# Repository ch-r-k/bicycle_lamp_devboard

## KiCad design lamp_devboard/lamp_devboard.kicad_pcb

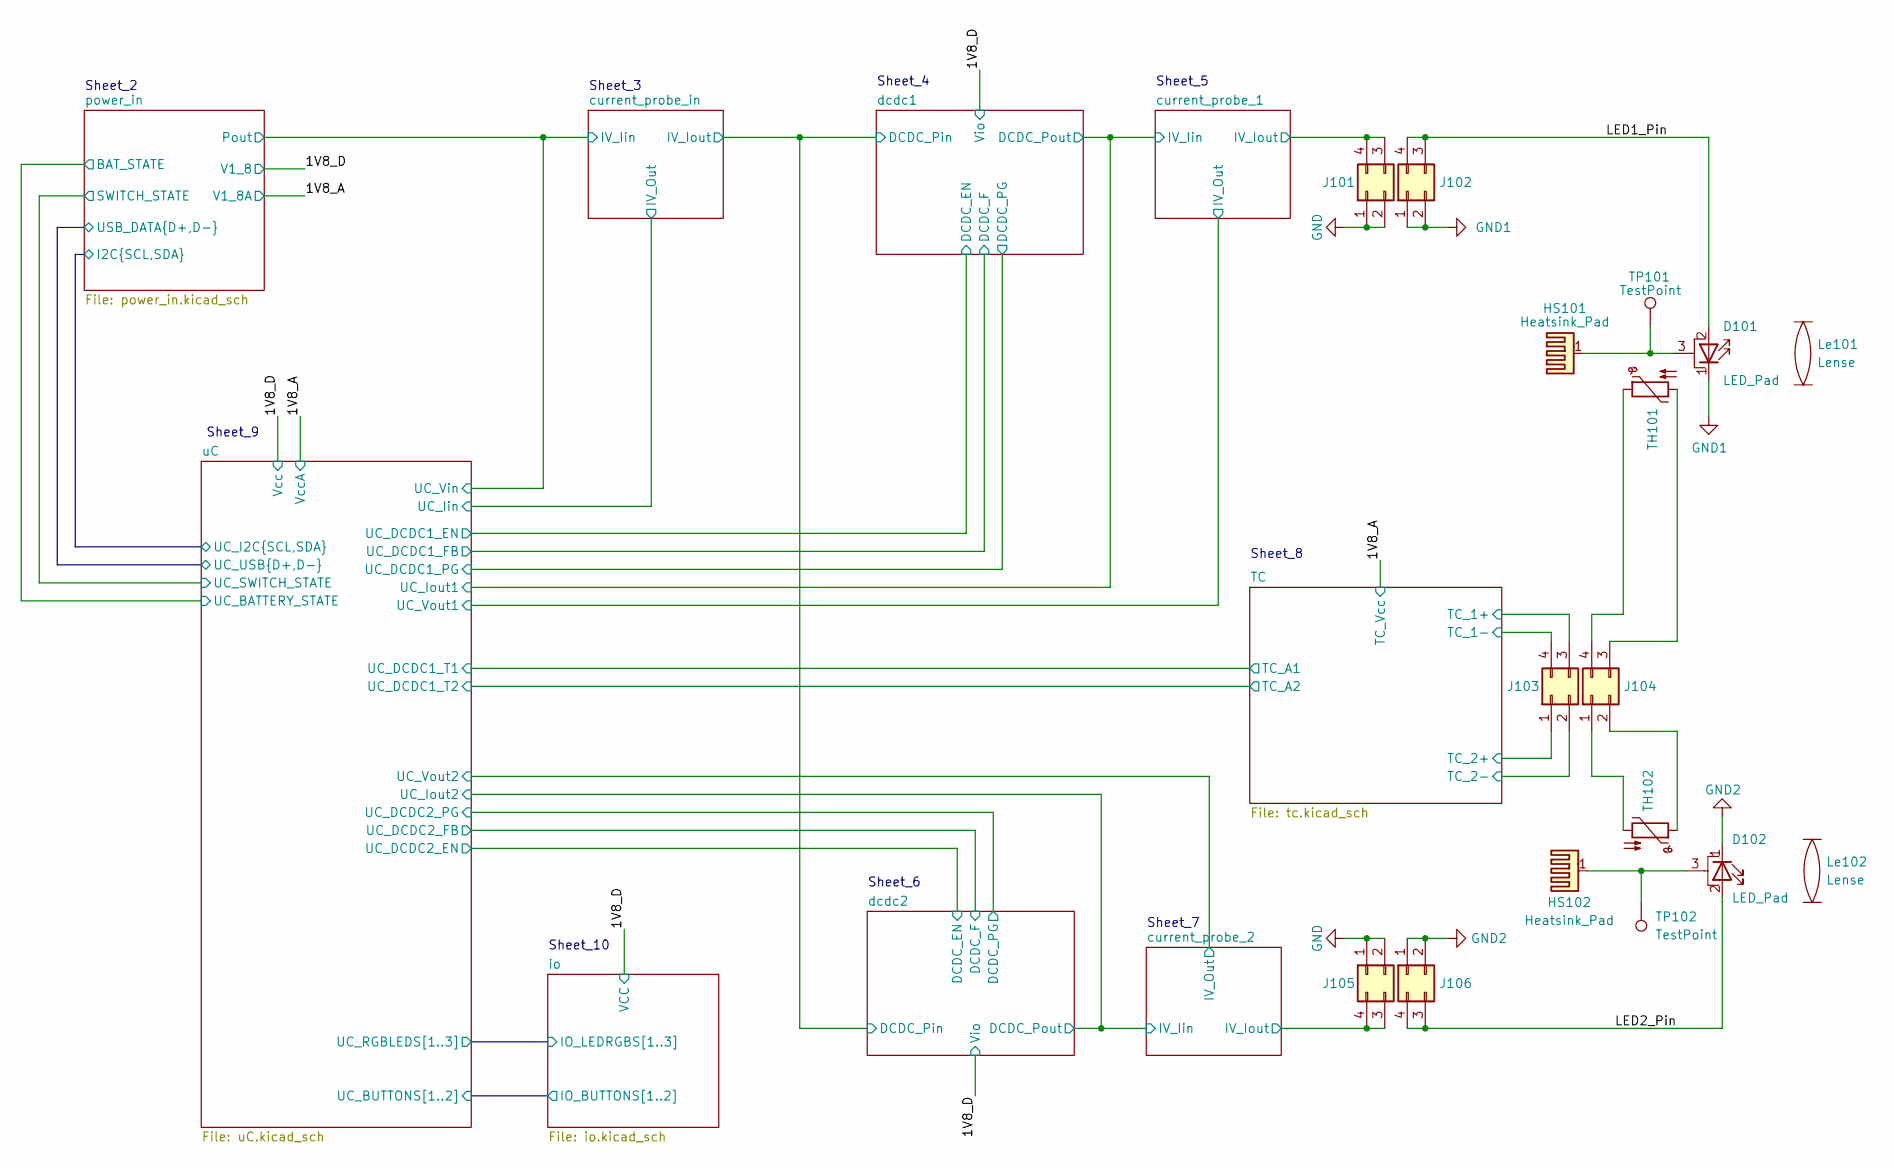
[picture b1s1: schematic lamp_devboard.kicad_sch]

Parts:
D101, D102: LED_Pad; LED_Cree-XHP50_6V
HS101, HS102: Heatsink_Pad; ATS-54190R-C1-R0
J101, J103, J105: Conn_02x02_Counter_Clockwise; PinSocket_2x02_P2.54mm_Horizontal
J102, J104, J106: Conn_02x02_Counter_Clockwise; PinHeader_2x02_P2.54mm_Vertical
Le101, Le102: Lense; EMILY
TH101, TH102: Thermistor_PTC; R_0805_2012Metric_Pad1.20x1.40mm_HandSolder
TP101, TP102: TestPoint; TestPoint_Pad_1.0x1.0mm

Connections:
/LED1_Pin: D101.2 (A), J102.3, J102.4
/LED2_Pin: D102.2 (A), J106.3, J106.4
/TC/TC_1+: J103.3; also elsewhere on the board
/TC/TC_2+: J103.1; also elsewhere on the board
/current_probe_1/IV_Iout: J101.3, J101.4; also elsewhere on the board
/current_probe_2/IV_Iout: J105.3, J105.4; also elsewhere on the board
GND1: D101.1 (K), J102.1, J102.2
unnamed: D101.3 (PAD), HS101.1, TP101.1
unnamed: D102.3 (PAD), HS102.1, TP102.1
unnamed: J104.1, TH102.2
unnamed: J104.2, TH102.1
unnamed: J104.3, TH101.2
unnamed: J104.4, TH101.1

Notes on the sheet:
Sheet_8
Sheet_9
Sheet_6
Sheet_5
Sheet_4
Sheet_10
Sheet_7
Sheet_2
Sheet_3

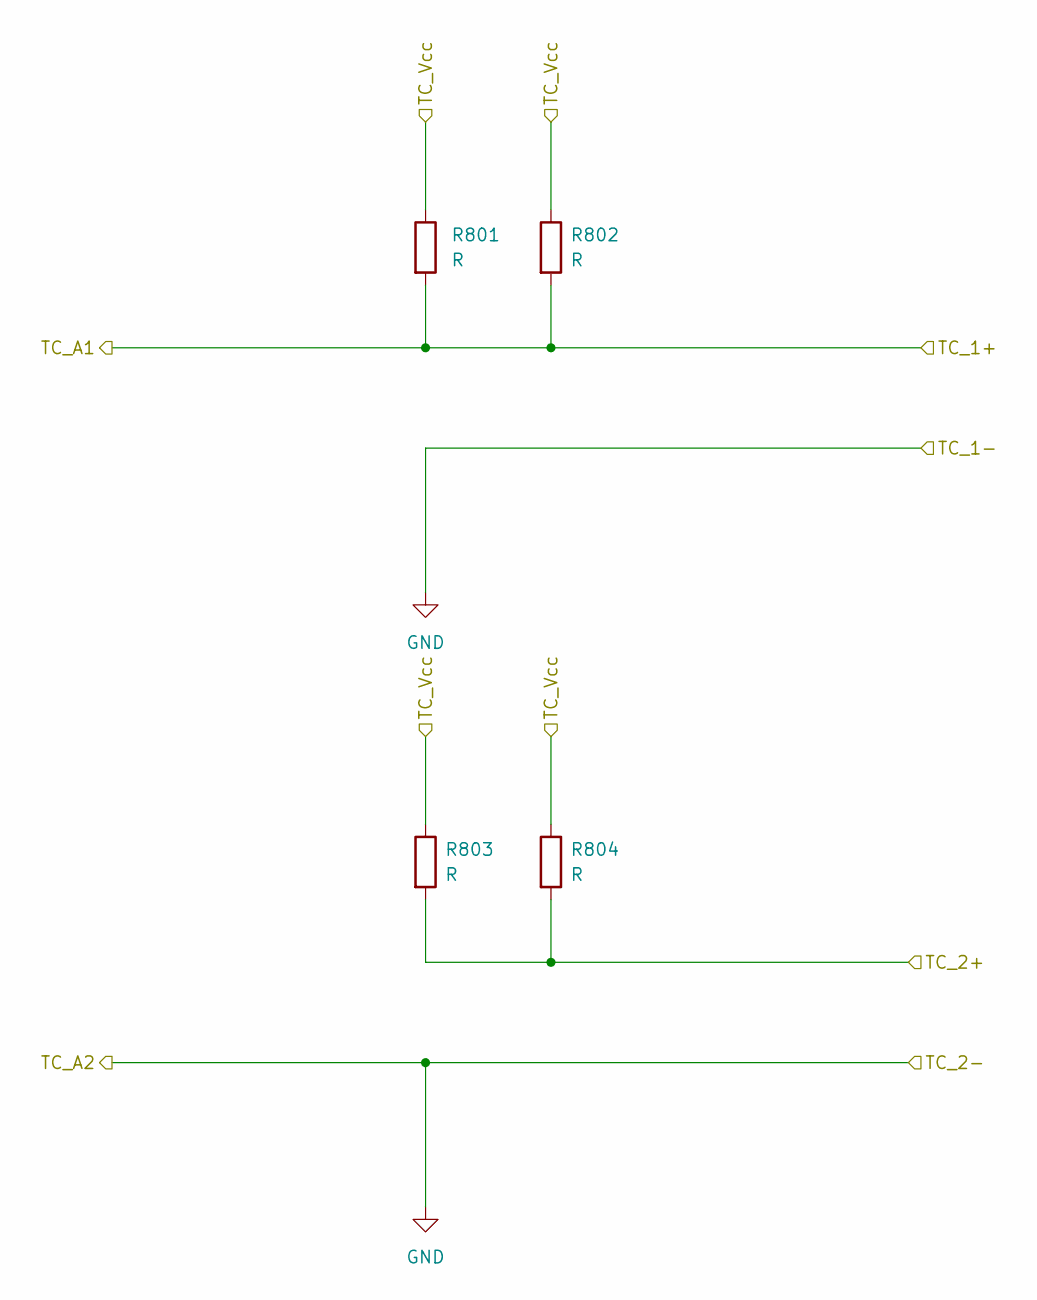
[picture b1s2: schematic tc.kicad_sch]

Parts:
R801, R802, R803, R804: R; R_0603_1608Metric_Pad0.98x0.95mm_HandSolder

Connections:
/1V8_A: R801.1, R802.1, R803.1, R804.1; also elsewhere on the board
/TC/TC_1+: R801.2, R802.2; also elsewhere on the board
/TC/TC_2+: R803.2, R804.2; also elsewhere on the board

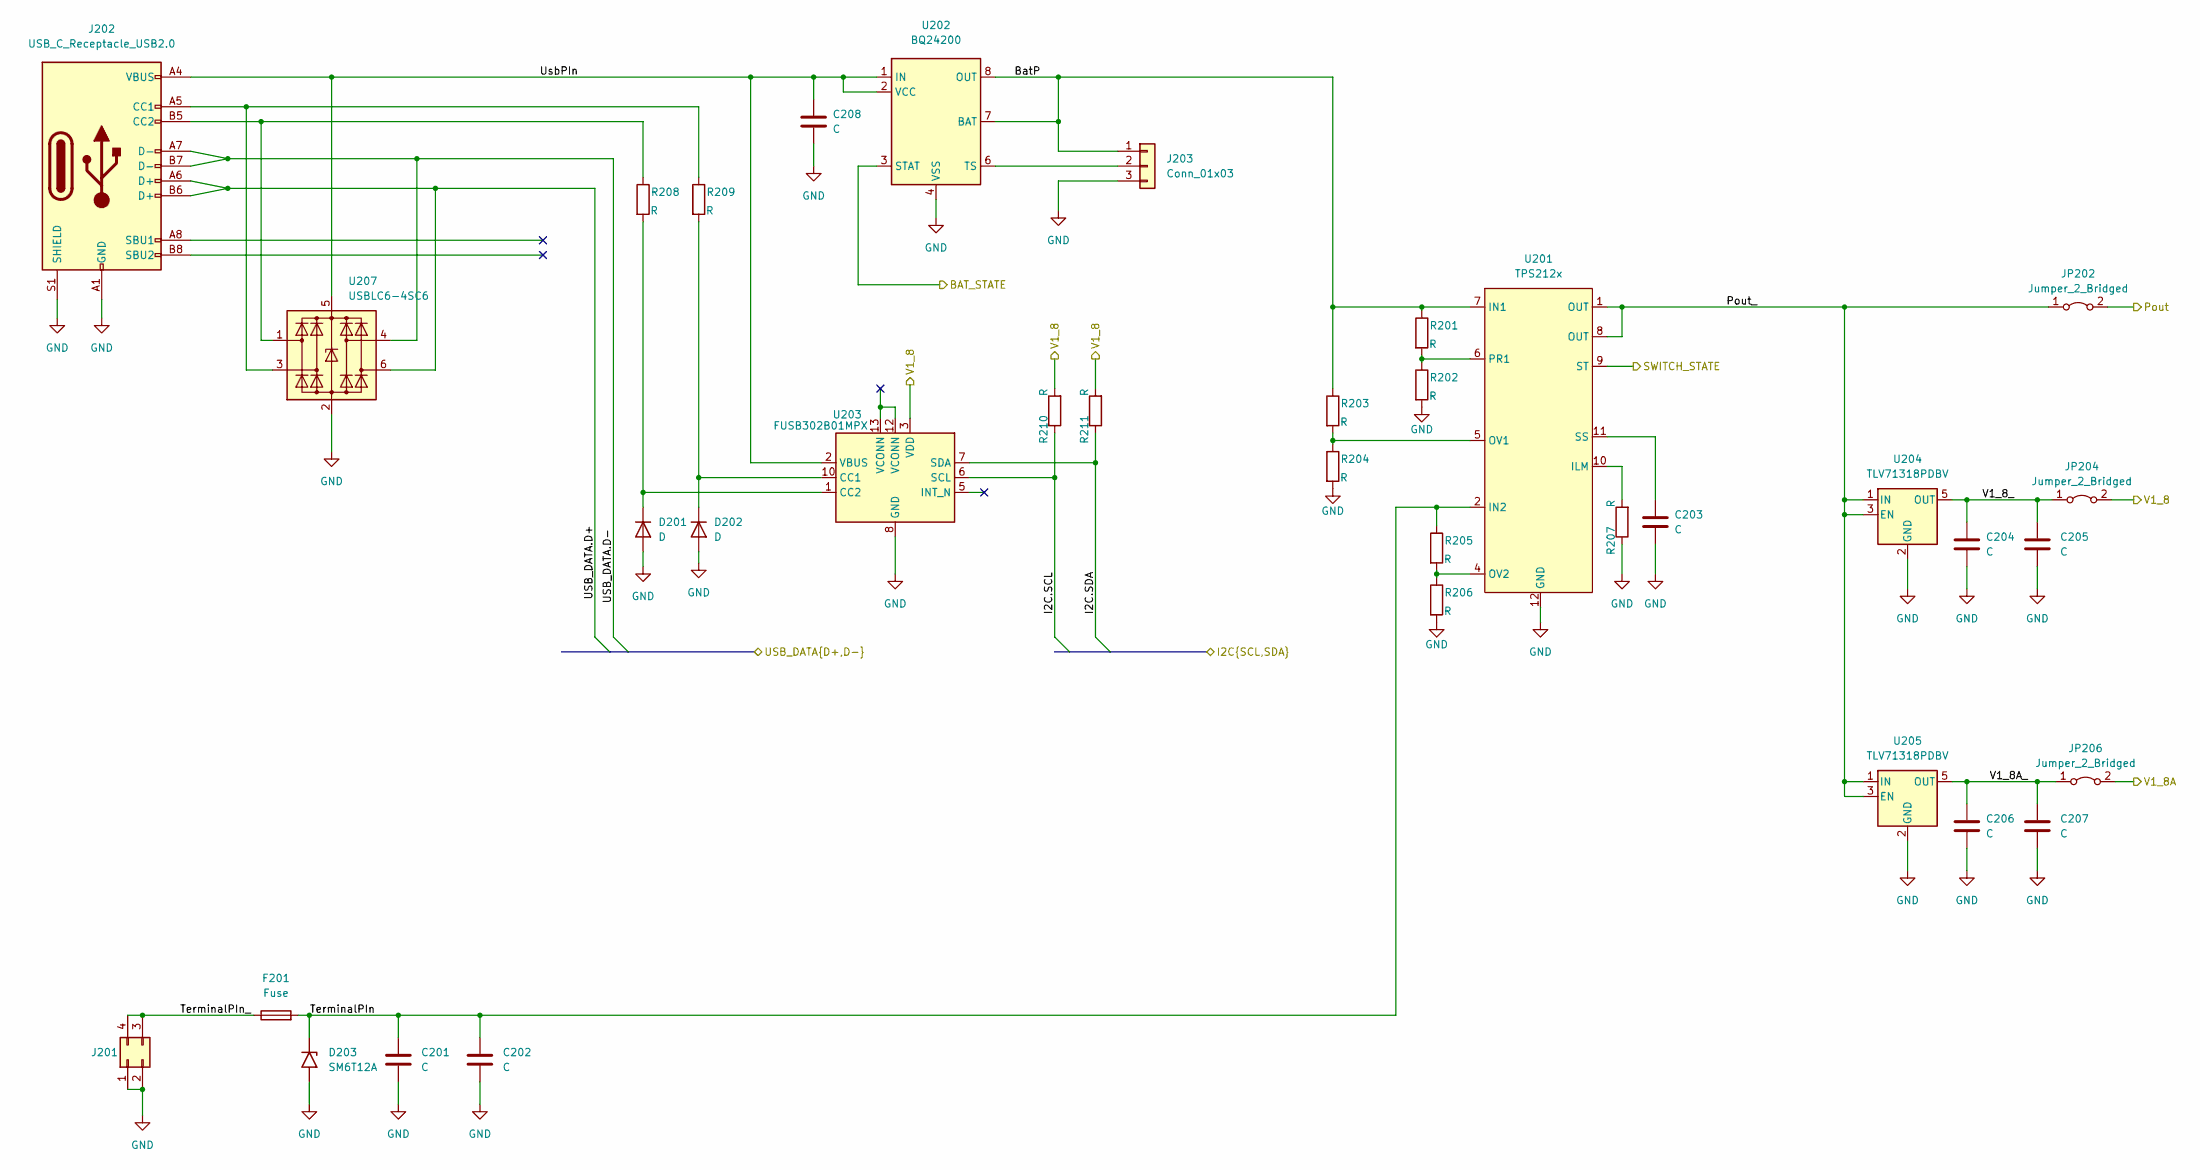
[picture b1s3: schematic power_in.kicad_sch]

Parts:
C201, C202, C203, C204, C206, C208: C; C_0603_1608Metric_Pad1.08x0.95mm_HandSolder
C205, C207: C; C_1206_3216Metric_Pad1.33x1.80mm_HandSolder
D201, D202: D; D_0603_1608Metric_Pad1.05x0.95mm_HandSolder
D203: SM6T12A; D_SMB
F201: Fuse; Fuse_1206_3216Metric_Pad1.42x1.75mm_HandSolder
J201: Conn_02x02_Counter_Clockwise; PinHeader_2x02_P2.54mm_Vertical
J202: USB_C_Receptacle_USB2.0; AMPHENOL_124018312112A
J203: Conn_01x03; Molex_KK-254_AE-6410-03A_1x03_P2.54mm_Vertical
JP202, JP204, JP206: Jumper_2_Bridged; SolderJumper-2_P1.3mm_Bridged_RoundedPad1.0x1.5mm
R201, R202, R203, R204, R205, R206, R207, R208, R209, R210, R211: R; R_0603_1608Metric_Pad0.98x0.95mm_HandSolder
U201: TPS212x; VQFN-HR
U202: BQ24200; HVSSOP-10-1EP_3x3mm_P0.5mm_EP1.57x1.88mm_ThermalVias
U203: FUSB302B01MPX; WQFN-14-1EP_2.5x2.5mm_P0.5mm_EP1.45x1.45mm
U204, U205: TLV71318PDBV; SOT-23-5
U207: USBLC6-4SC6; SOT-23-6

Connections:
/1V8_A: JP206.2 (B); also elsewhere on the board
/current_probe_in/IV_Iin: JP202.2 (B); also elsewhere on the board
/power_in/BAT_STATE: U202.3 (STAT); also elsewhere on the board
/power_in/BatP: J203.1, R201.1, R203.1, U201.7 (IN1), U202.7 (BAT), U202.8 (OUT)
/power_in/I2C.SCL: R210.1, U203.6 (SCL); also elsewhere on the board
/power_in/I2C.SDA: R211.1, U203.7 (SDA); also elsewhere on the board
/power_in/Pout_: JP202.1 (A), U201.1 (OUT), U201.8 (OUT), U204.1 (IN), U204.3 (EN), U205.1 (IN), U205.3 (EN)
/power_in/SWITCH_STATE: U201.9 (ST); also elsewhere on the board
/power_in/TerminalPIn: C201.1, C202.1, D203.1 (A1), F201.2, R205.1, U201.2 (IN2)
/power_in/TerminalPIn_: F201.1, J201.3, J201.4
/power_in/USB_DATA.D+: J202.A6 (D+), J202.B6 (D+), U207.6 (I/O4); also elsewhere on the board
/power_in/USB_DATA.D-: J202.A7 (D-), J202.B7 (D-), U207.4 (I/O3); also elsewhere on the board
/power_in/UsbPIn: C208.1, J202.A4 (VBUS), J202.A9 (VBUS), J202.B4 (VBUS), J202.B9 (VBUS), U202.1 (IN), U202.2 (VCC), U203.2 (VBUS), U207.5 (VBUS)
/power_in/V1_8A_: C206.1, C207.1, JP206.1 (A), U205.5 (OUT)
/power_in/V1_8_: C204.1, C205.1, JP204.1 (A), U204.5 (OUT)
unnamed: C203.1, U201.11 (SS)
unnamed: D201.1 (K), R208.2, U203.1 (CC2), U203.14 (CC2)
unnamed: D202.1 (K), R209.2, U203.10 (CC1), U203.11 (CC1)
unnamed: J202.A5 (CC1), R209.1, U207.3 (I/O2)
unnamed: J202.B5 (CC2), R208.1, U207.1 (I/O1)
unnamed: J203.2, U202.6 (TS)
unnamed: R201.2, R202.1, U201.6 (PR1)
unnamed: R203.2, R204.1, U201.5 (OV1)
unnamed: R205.2, R206.1, U201.4 (OV2)
unnamed: R207.2, U201.10 (ILM)

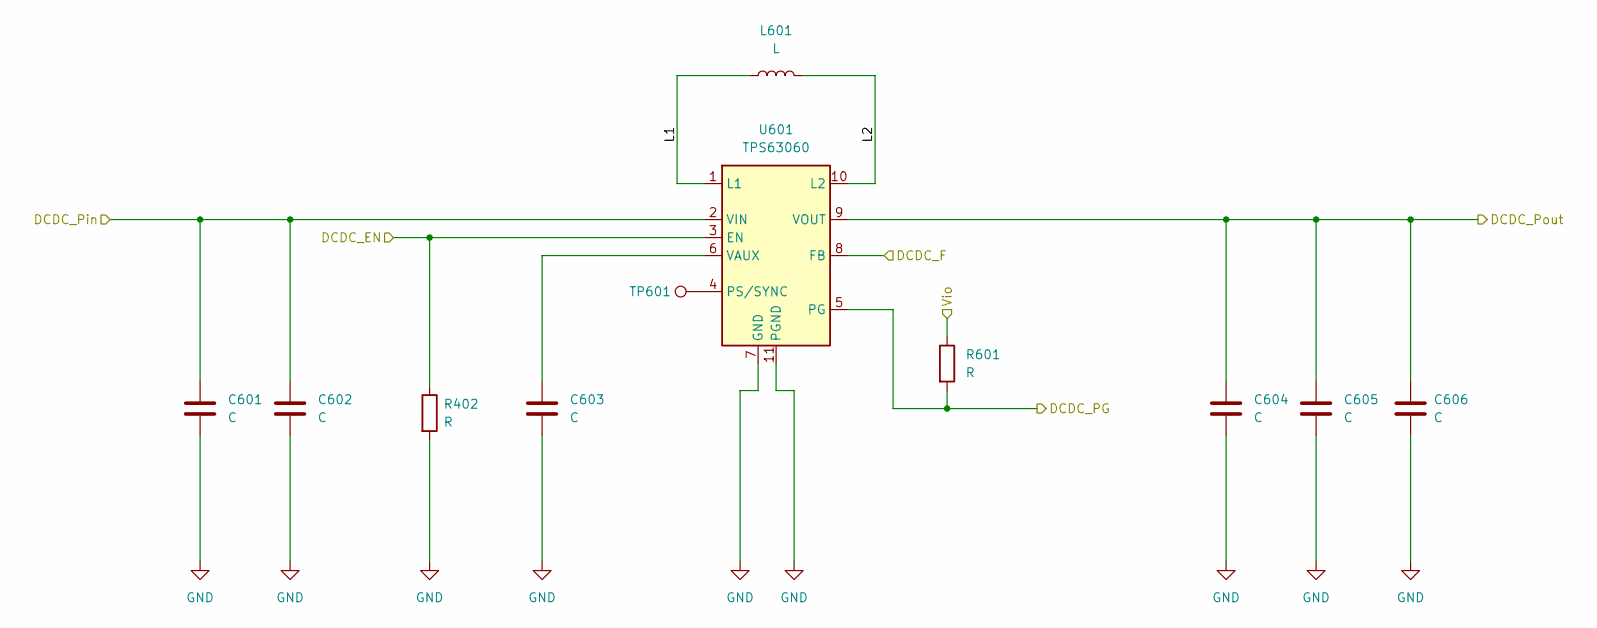
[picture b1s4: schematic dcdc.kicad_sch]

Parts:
C601, C604, C605, C606: C; C_1206_3216Metric_Pad1.33x1.80mm_HandSolder
C602, C603: C; C_0603_1608Metric_Pad1.08x0.95mm_HandSolder
L601: L; L_Coilcraft_XxL4020
R402, R601: R; R_0603_1608Metric_Pad0.98x0.95mm_HandSolder
TP601: TestPoint; TestPoint_Pad_1.0x1.0mm
U601: TPS63060; Texas_S-PWSON-N10_ThermalVias

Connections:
/current_probe_2/IV_Iin: C604.1, C605.1, C606.1, U601.9 (VOUT); also elsewhere on the board
/current_probe_in/IV_Iout: C601.1, C602.1, U601.2 (VIN); also elsewhere on the board
/dcdc2/DCDC_F: U601.8 (FB); also elsewhere on the board
/dcdc2/DCDC_PG: R601.2, U601.5 (PG); also elsewhere on the board
/dcdc2/L1: L601.1, U601.1 (L1)
/dcdc2/L2: L601.2, U601.10 (L2)
unnamed: C603.1, U601.6 (VAUX)
unnamed: TP601.1, U601.4 (PS/SYNC)

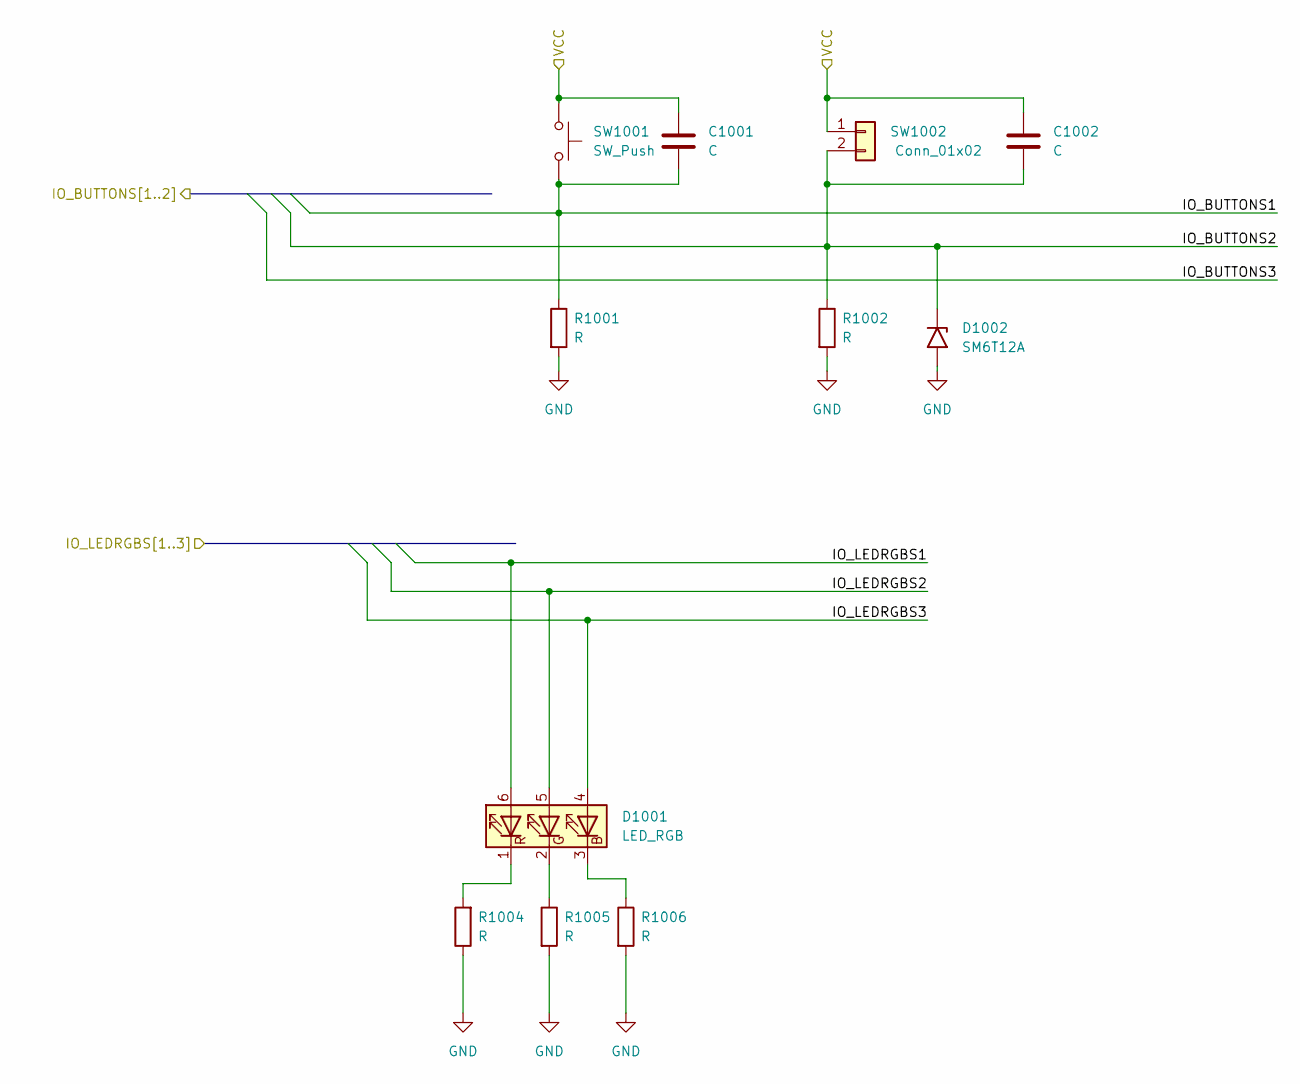
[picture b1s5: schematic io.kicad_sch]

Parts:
C1001, C1002: C; C_0603_1608Metric_Pad1.08x0.95mm_HandSolder
D1001: LED_RGB; LED_WS2812_PLCC6_5.0x5.0mm_P1.6mm
D1002: SM6T12A; D_SMB
R1001, R1002, R1004, R1005, R1006: R; R_0603_1608Metric_Pad0.98x0.95mm_HandSolder
SW1001: SW_Push; SW_Push_1P1T_NO_CK_KMR2
SW1002: Conn_01x02; PinHeader_1x02_P2.54mm_Vertical

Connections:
/io/IO_BUTTONS1: C1001.2, R1001.1, SW1001.2; also elsewhere on the board
/io/IO_BUTTONS2: C1002.2, D1002.1 (A1), R1002.1, SW1002.2; also elsewhere on the board
/io/IO_LEDRGBS1: D1001.6 (RA); also elsewhere on the board
/io/IO_LEDRGBS2: D1001.5 (GA); also elsewhere on the board
/io/IO_LEDRGBS3: D1001.4 (BA); also elsewhere on the board
unnamed: D1001.1 (RK), R1004.2
unnamed: D1001.2 (GK), R1005.1
unnamed: D1001.3 (BK), R1006.1

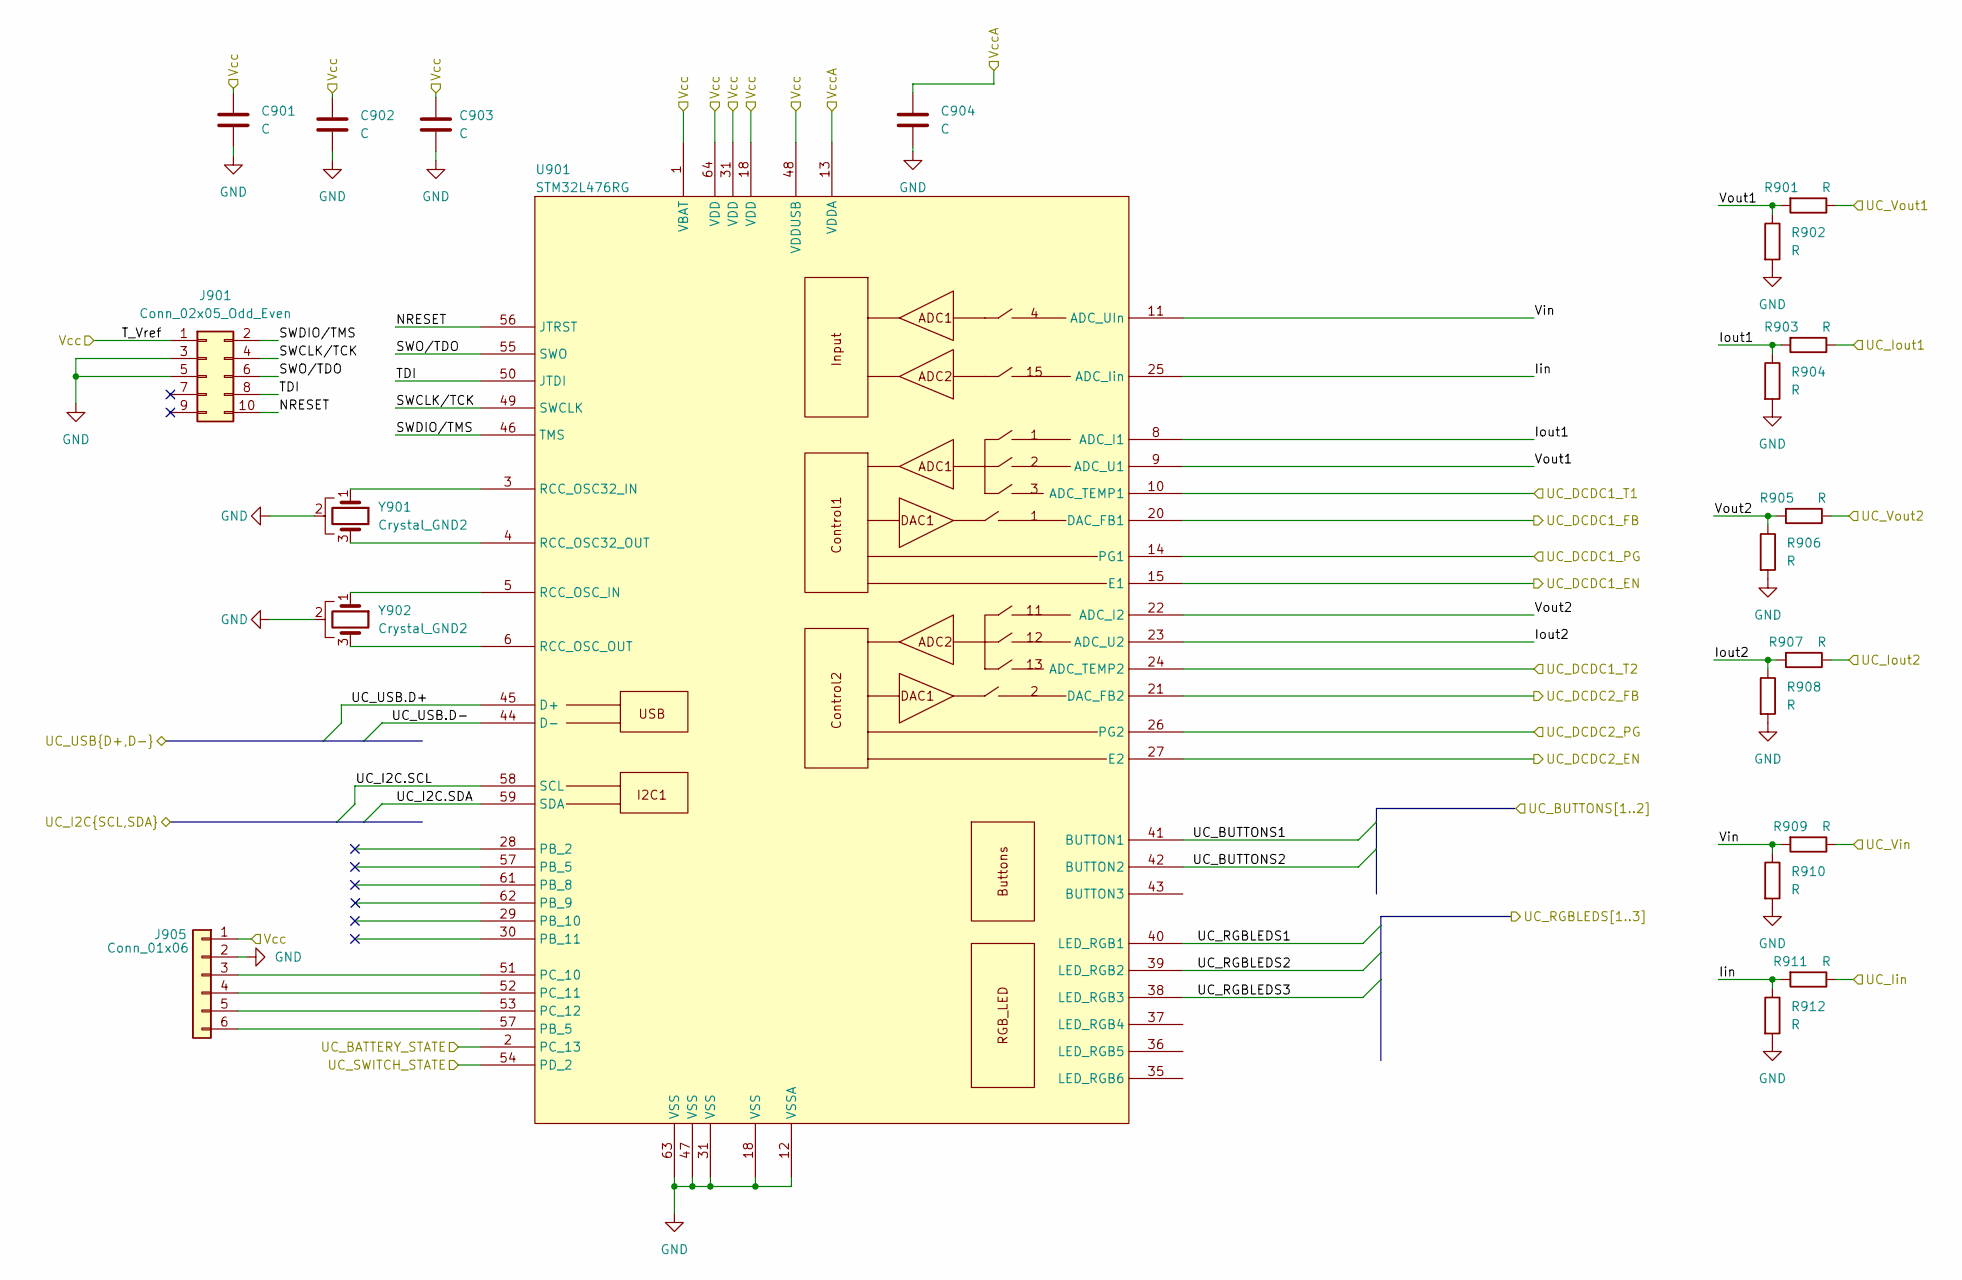
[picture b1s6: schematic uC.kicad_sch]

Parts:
C901, C902, C903, C904: C; C_0603_1608Metric_Pad1.08x0.95mm_HandSolder
J901: Conn_02x05_Odd_Even; PinSocket_2x05_P1.27mm_Vertical_SMD
J905: Conn_01x06; PinHeader_1x06_P2.54mm_Vertical
R901, R902, R903, R904, R905, R906, R907, R908, R909, R910, R911, R912: R; R_0603_1608Metric_Pad0.98x0.95mm_HandSolder
U901: STM32L476RG; LQFP-64_10x10mm_P0.5mm
Y901, Y902: Crystal_GND2; Crystal_SMD_3225-4Pin_3.2x2.5mm_HandSoldering

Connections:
/1V8_A: C904.1, U901.13 (VDDA); also elsewhere on the board
/TC/TC_1+: U901.10 (ADC_TEMP1); also elsewhere on the board
/current_probe_1/IV_Iin: R903.1; also elsewhere on the board
/current_probe_1/IV_Out: R901.1; also elsewhere on the board
/current_probe_2/IV_Iin: R907.1; also elsewhere on the board
/current_probe_2/IV_Out: R905.1; also elsewhere on the board
/current_probe_in/IV_Iin: R909.1; also elsewhere on the board
/current_probe_in/IV_Out: R911.1; also elsewhere on the board
/dcdc1/DCDC_F: U901.20 (DAC_FB1); also elsewhere on the board
/dcdc1/DCDC_PG: U901.14 (PG1); also elsewhere on the board
/dcdc2/DCDC_F: U901.21 (DAC_FB2); also elsewhere on the board
/dcdc2/DCDC_PG: U901.26 (PG2); also elsewhere on the board
/io/IO_BUTTONS1: U901.41 (BUTTON1); also elsewhere on the board
/io/IO_BUTTONS2: U901.42 (BUTTON2); also elsewhere on the board
/io/IO_LEDRGBS1: U901.40 (LED_RGB1); also elsewhere on the board
/io/IO_LEDRGBS2: U901.39 (LED_RGB2); also elsewhere on the board
/io/IO_LEDRGBS3: U901.38 (LED_RGB3); also elsewhere on the board
/power_in/BAT_STATE: U901.2 (PC_13); also elsewhere on the board
/power_in/I2C.SCL: U901.58 (SCL); also elsewhere on the board
/power_in/I2C.SDA: U901.59 (SDA); also elsewhere on the board
/power_in/SWITCH_STATE: U901.54 (PD_2); also elsewhere on the board
/power_in/USB_DATA.D+: U901.45 (D+); also elsewhere on the board
/power_in/USB_DATA.D-: U901.44 (D-); also elsewhere on the board
/uC/Iin: R911.2, R912.1, U901.25 (ADC_Iin)
/uC/Iout1: R903.2, R904.1, U901.8 (ADC_I1)
/uC/Iout2: R907.2, R908.1, U901.23 (ADC_U2)
/uC/NRESET: J901.10, U901.56 (JTRST)
/uC/SWCLK/TCK: J901.4, U901.49 (SWCLK)
/uC/SWDIO/TMS: J901.2, U901.46 (TMS)
/uC/SWO/TDO: J901.6, U901.55 (SWO)
/uC/TDI: J901.8, U901.50 (JTDI)
/uC/Vin: R909.2, R910.1, U901.11 (ADC_UIn)
/uC/Vout1: R901.2, R902.1, U901.9 (ADC_U1)
/uC/Vout2: R905.2, R906.1, U901.22 (ADC_I2)
unnamed: J905.3, U901.51 (PC_10)
unnamed: J905.4, U901.52 (PC_11)
unnamed: J905.5, U901.53 (PC_12)
unnamed: J905.6, U901.57 (PB_5)
unnamed: U901.3 (RCC_OSC32_IN), Y901.1
unnamed: U901.4 (RCC_OSC32_OUT), Y901.3
unnamed: U901.5 (RCC_OSC_IN), Y902.1
unnamed: U901.6 (RCC_OSC_OUT), Y902.3

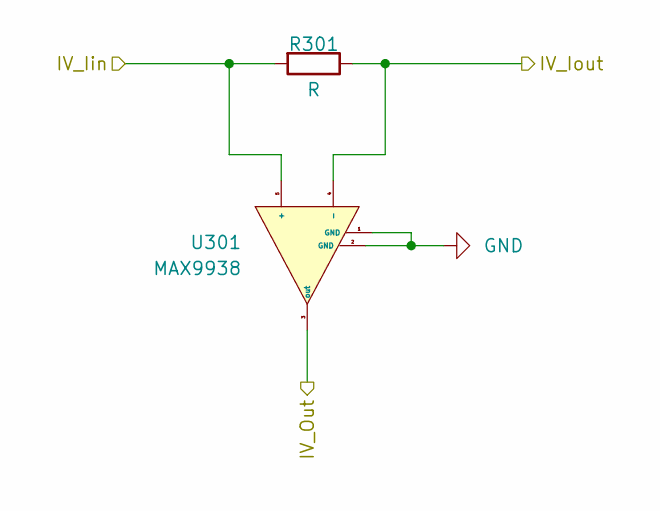
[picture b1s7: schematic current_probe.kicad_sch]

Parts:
R301: R; R_1210_3225Metric_Pad1.30x2.65mm_HandSolder
U301: MAX9938; SOT-23-5_HandSoldering

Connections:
/current_probe_in/IV_Iin: R301.2, U301.5 (+); also elsewhere on the board
/current_probe_in/IV_Iout: R301.1, U301.4 (-); also elsewhere on the board
/current_probe_in/IV_Out: U301.3 (out); also elsewhere on the board

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
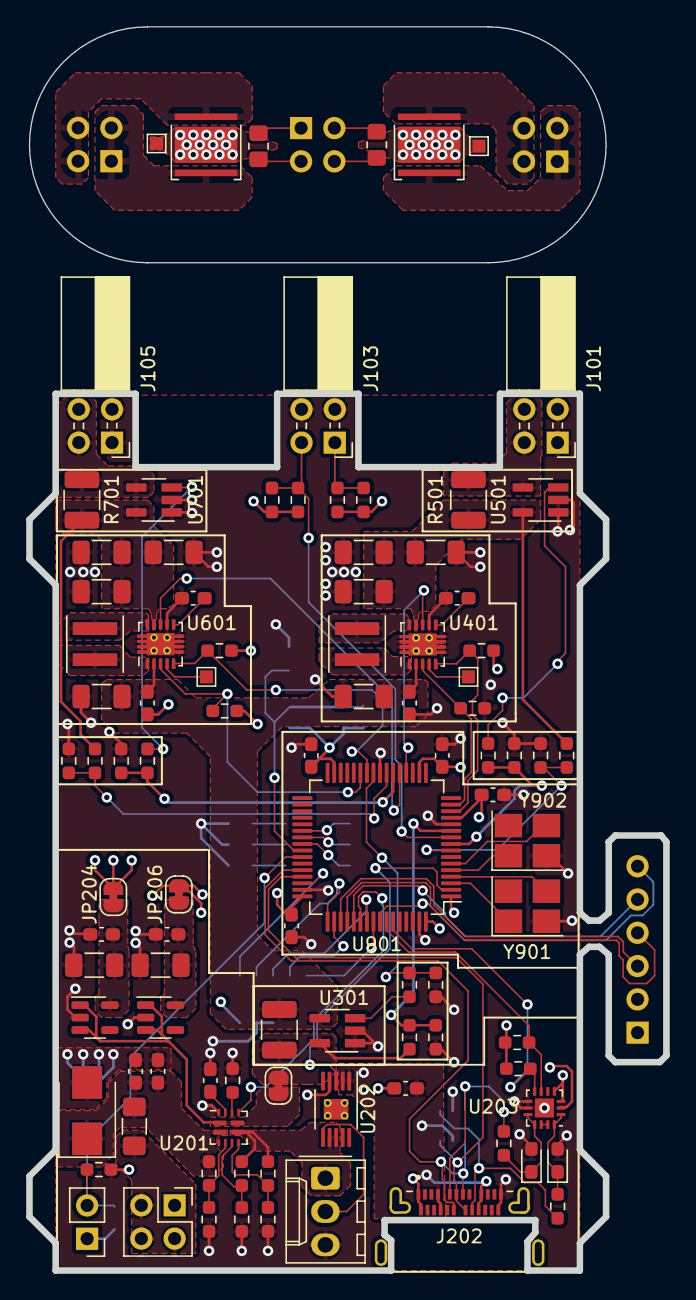
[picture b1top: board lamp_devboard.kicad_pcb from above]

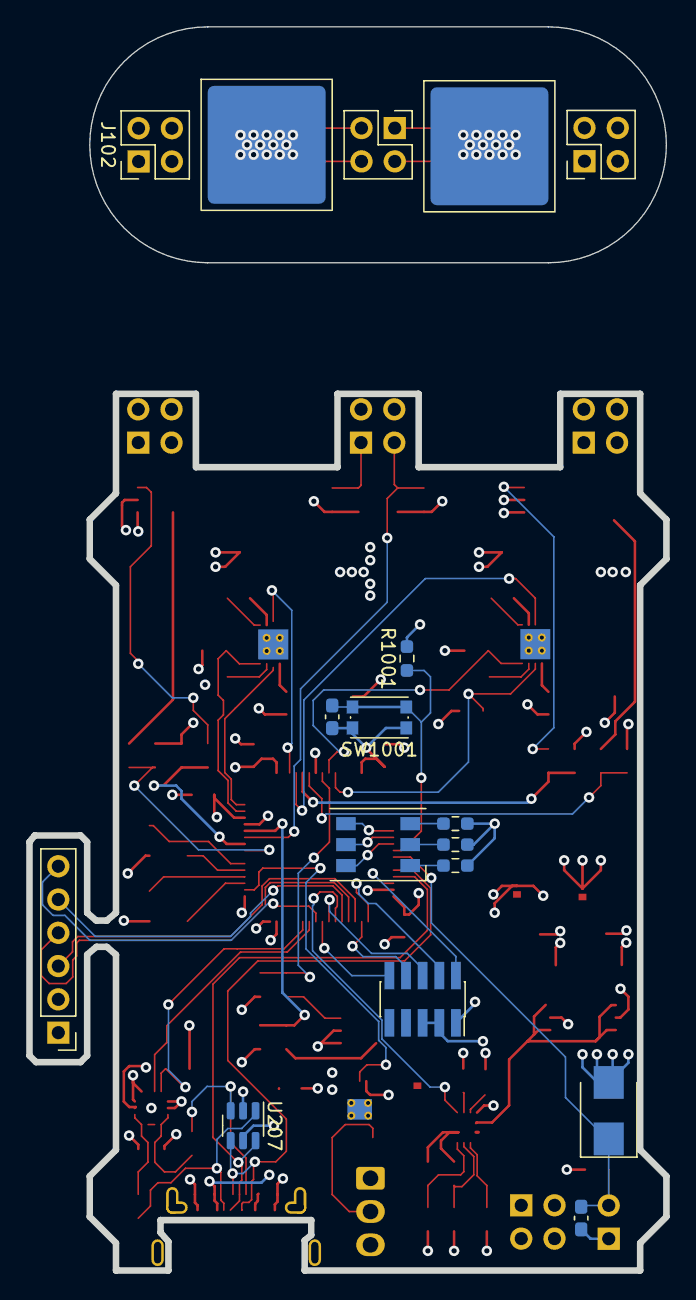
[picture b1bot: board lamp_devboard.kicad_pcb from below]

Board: 4 copper layers, 48.6 x 94.7 mm, 113 parts (17 on the bottom side), 88 nets.

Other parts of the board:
C401, C404, C405, C406: C; C_1206_3216Metric_Pad1.33x1.80mm_HandSolder
C402, C403: C; C_0603_1608Metric_Pad1.08x0.95mm_HandSolder
L401: L; L_Coilcraft_XxL4020
R401, R602: R; R_0603_1608Metric_Pad0.98x0.95mm_HandSolder
R501, R701: R; R_1210_3225Metric_Pad1.30x2.65mm_HandSolder
TP401: TestPoint; TestPoint_Pad_1.0x1.0mm
U401: TPS63060; Texas_S-PWSON-N10_ThermalVias
U501, U701: MAX9938; SOT-23-5_HandSoldering

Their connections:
/current_probe_1/IV_Iin: C404.1, C405.1, C406.1, R501.2, U401.9 (VOUT), U501.5 (+); also elsewhere on the board
/current_probe_1/IV_Iout: R501.1, U501.4 (-); also elsewhere on the board
/current_probe_1/IV_Out: U501.3 (out); also elsewhere on the board
/current_probe_2/IV_Iin: R701.2, U701.5 (+); also elsewhere on the board
/current_probe_2/IV_Iout: R701.1, U701.4 (-); also elsewhere on the board
/current_probe_2/IV_Out: U701.3 (out); also elsewhere on the board
/current_probe_in/IV_Iout: C401.1, C402.1, U401.2 (VIN); also elsewhere on the board
/dcdc1/DCDC_F: U401.8 (FB); also elsewhere on the board
/dcdc1/DCDC_PG: R401.2, U401.5 (PG); also elsewhere on the board
/dcdc1/L1: L401.1, U401.1 (L1)
/dcdc1/L2: L401.2, U401.10 (L2)
unnamed: C403.1, U401.6 (VAUX)
unnamed: TP401.1, U401.4 (PS/SYNC)

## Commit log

2023-10-25 first schematic design
2023-10-25 small changes in schematic
2023-11-01 schematics, add battery to power module
2023-11-04 place components
2023-11-05 add some power polygones to the pcb
2023-11-07 add net classes, working on pcb layout
2023-11-10 some changes
2023-11-22 some small changes
2023-12-02 first version of the pcb board
